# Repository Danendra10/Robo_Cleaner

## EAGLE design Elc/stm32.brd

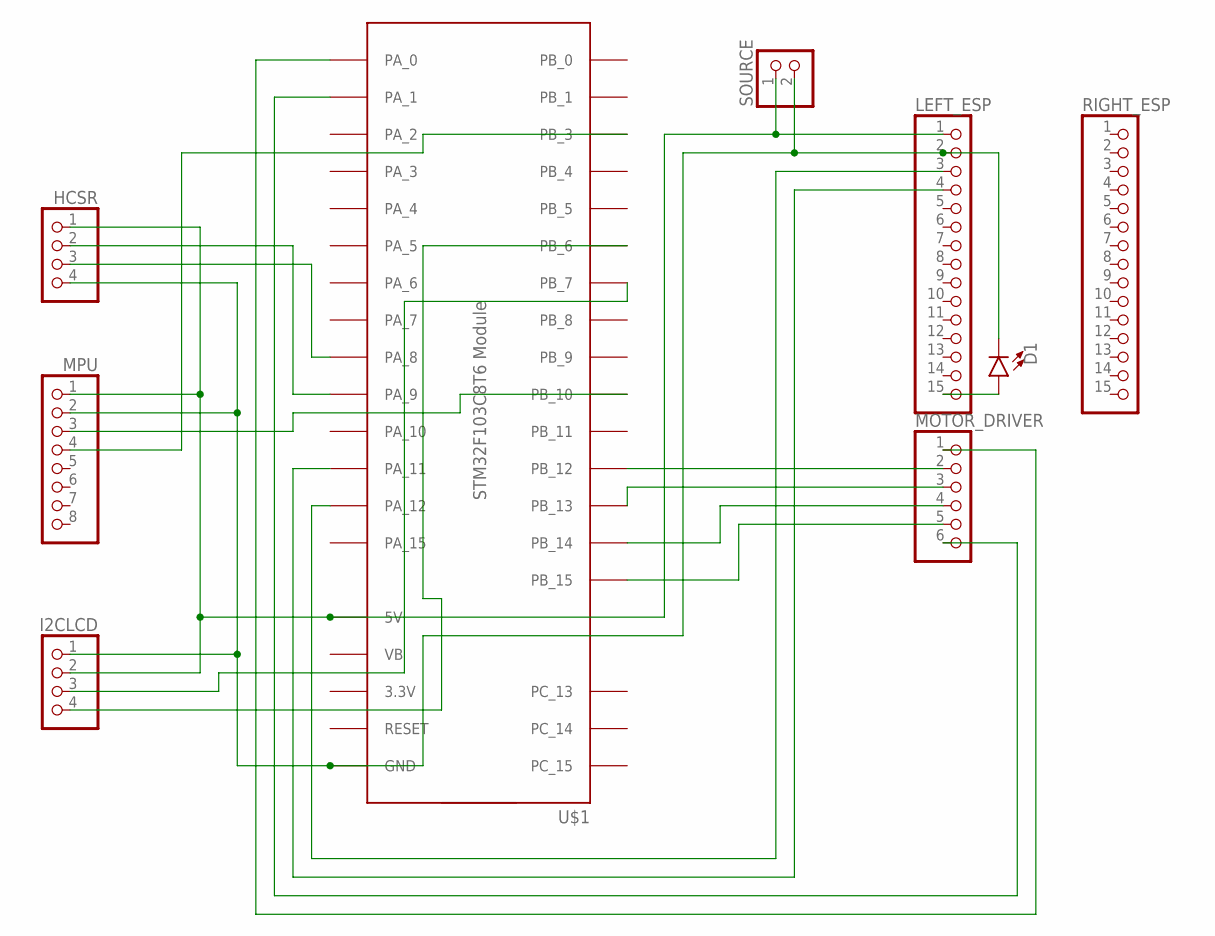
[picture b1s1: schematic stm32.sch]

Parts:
D1: LED-3MM-NO_SILK; LED_3MM-NS
HCSR: PINHD-1X4; 1X04
I2CLCD: PINHD-1X4; 1X04
LEFT_ESP: PINHD-1X15; 1X15
MOTOR_DRIVER: PINHD-1X6; 1X06
MPU: PINHD-1X8; 1X08
RIGHT_ESP: PINHD-1X15; 1X15
SOURCE: PINHD-1X2; 1X02
U$1: STM32F103C8T6-MODULE

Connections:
unnamed: HCSR.1, I2CLCD.2, LEFT_ESP.1, MPU.1, SOURCE.1, U$1.5V
unnamed: LEFT_ESP.3, U$1.PA_12
unnamed: LEFT_ESP.4, U$1.PA_11
unnamed: MOTOR_DRIVER.1, U$1.PA_0
unnamed: MOTOR_DRIVER.6, U$1.PA_1
unnamed: MOTOR_DRIVER.3, U$1.PB_13
unnamed: D1.A, LEFT_ESP.15
unnamed: D1.K (C), HCSR.4, I2CLCD.1, LEFT_ESP.2, MPU.2, SOURCE.2, U$1.GND@1 (GND), U$1.GND@2 (GND), U$1.GND@3 (GND)
unnamed: MOTOR_DRIVER.2, U$1.PB_12
unnamed: MOTOR_DRIVER.4, U$1.PB_14
unnamed: MOTOR_DRIVER.5, U$1.PB_15
unnamed: I2CLCD.3, U$1.PB_7
unnamed: I2CLCD.4, U$1.PB_6
unnamed: MPU.3, U$1.PB_10
unnamed: MPU.4, U$1.PB_3
unnamed: HCSR.2, U$1.PA_9
unnamed: HCSR.3, U$1.PA_8

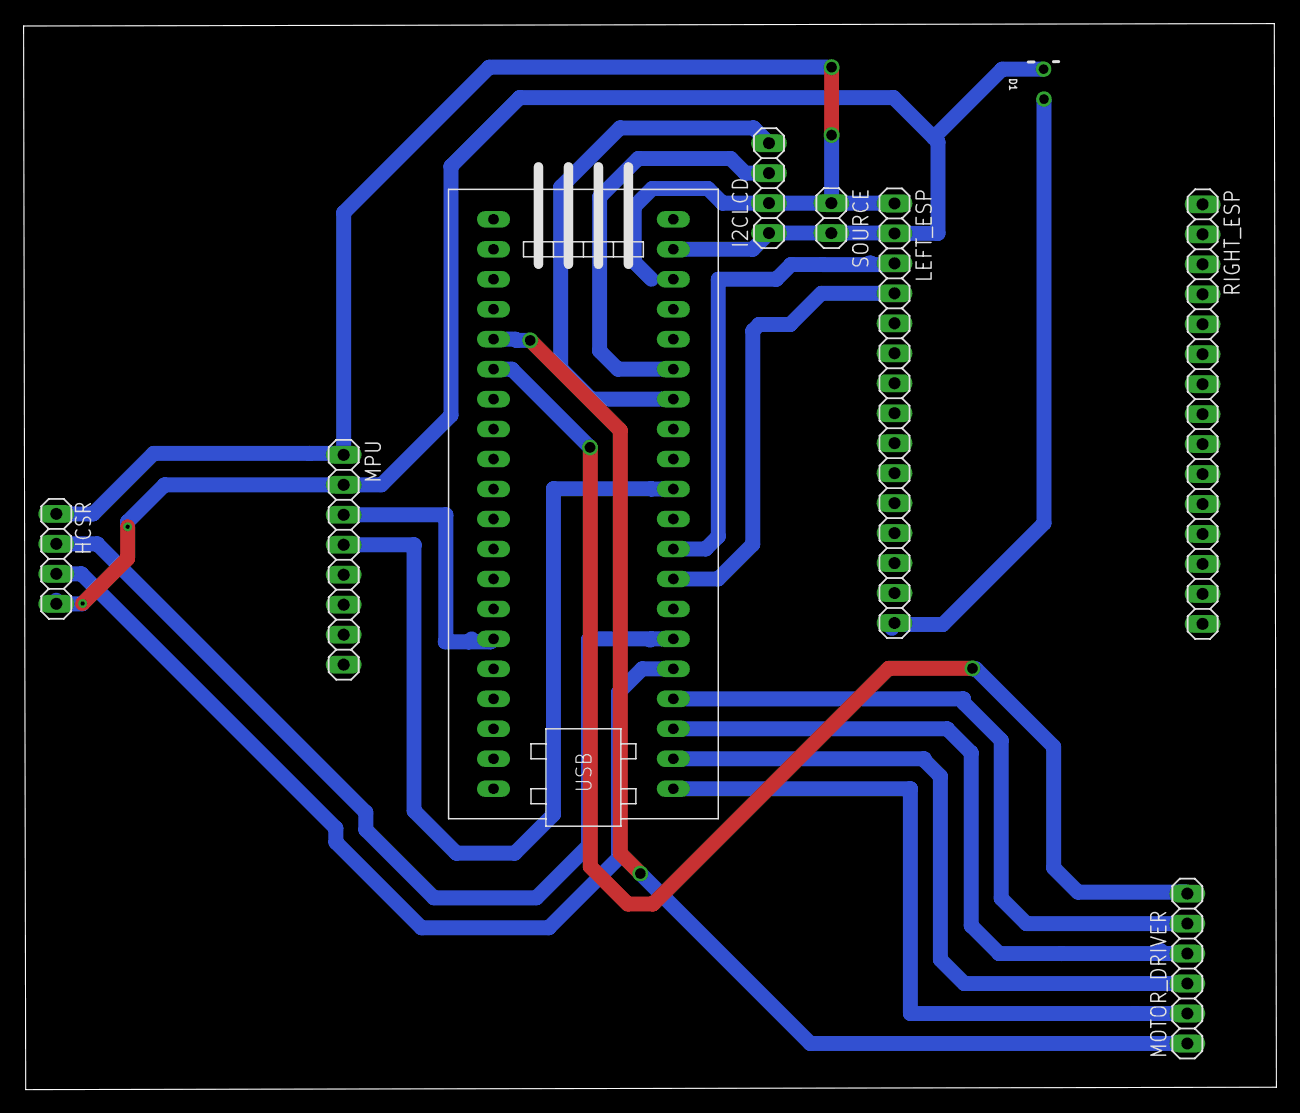
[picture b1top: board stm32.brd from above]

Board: 2 copper layers, 106.2 x 90.3 mm, 9 parts (0 on the bottom side), 17 nets.

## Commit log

2022-12-08 commit all
2023-02-27 Create LICENSE

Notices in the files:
parts and their libraries:
SparkFun-LED: Licensing: Creative Commons ShareAlike 4.0 International - https://creativecommons.org/licenses/by-sa/4.0
